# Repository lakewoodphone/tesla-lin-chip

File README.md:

# tesla-lin-chip

Tesla LIN reverse-engineering and anti-nag chip project. Covers passive LIN capture, active frame injection, Model 3/Y/X steering wheel volume control, and the custom dual-LIN ESP32-S3 Rev A PCB (JLCPCB order).

**Local path:** `C:\Users\ezabz\Code\tesla-lin-chip`
**GitHub:** `https://github.com/lakewoodphone/tesla-lin-chip`

Start with `START_HERE.md` when resuming. It now points to the current Rev A ESP32-S3 dual-LIN Model 3 active anti-nag path. Older XIAO/APG discovery notes are preserved under `docs/archive/legacy-xiao-2026-06-17/` and should be treated as historical evidence, not the active operating surface.

Current first-read docs:

```text
START_HERE.md
NEXT_STEPS.md
TOOLS.md
docs/README.md
docs/active/rev-a-model3-active-anti-nag.md
docs/active/model3-capture-data-index.md
```

Current Rev A helper:

```powershell
powershell -NoProfile -ExecutionPolicy Bypass -File tools\rev-a-active-model3.ps1 -Action Preflight
```

For the implementation plan that makes the bench, passive car testing, and final active-capable chip more robust, read `IMPLEMENTATION_ROADMAP.md`.

## Current Status

- Passive LIN receive is bench-verified at 19200 baud.
- Full no-car evidence passed on 2026-05-26 and again after APG reseat on 2026-05-27: 80/80 exact APG -> XIAO matches across raw IDs `0x00` through `0x3F`, with 0 APG failures.
- Active Model X bench TX is verified on the isolated bench. `model:x` + `antinag:start` produced more than 100 self-received `0x0C` frames with enhanced checksum and parity OK.
- Active improvements applied: bus-idle collision guard (2 ms silence before TX), realistic scroll payloads (non-zero B2/B3), and mirror/alive frame injection (`0x0D` at 500 ms via `mirror:on`).
- Active safety now reports reset reason, fault count, last fault, and lockout state. RX-integrity spikes or a dominant-line timeout while armed force active output off and block re-arm until `safe:off` is run after inspection.
- Repository default now builds `field_passive`; active TX is explicit via `bench_active_ble` or `chip_lab_active`.
- BLE service "TeslaAntiNag" in active builds exposes model (x/3/y/auto), mode (duty/always), period (5-120s), enable (on/off), status, and capabilities characteristics. Enable requires `safe:arm` first.
- BLE advertising was revalidated on 2026-05-27 after fixing invalid NimBLE advertising intervals; active lab builds report `advertising=yes` over serial.
- Car-day tooling enforces passive preflight and verifies `field_passive` firmware by default.
- APG known-ID raw fallback captures XIAO-generated active Model X frames after APG reseat: `active-apg-raw-proof.ps1` passed with 11 raw `ID=0x0C PID=0x4C` rows at `logs\lin-capture-20260527_212130.csv`.
- Model 3/Y steering LIN was captured on 2026-05-28. The confirmed left wheel control ID is `0x2A` (7 bytes) and right wheel control ID is `0x2B` (6 bytes). Left wheel byte[0] is `0x0D` volume up, `0x0B` volume down, `0x2C` click, `0x0C` idle. See `docs/model3y-steering-lin-2026-05-28.md`.
- `car_passthrough` is a new dual-transceiver firmware profile for the actual cut-wire bridge design. See `docs/model3y-passthrough-volume.md`.
- Final active-use hardware requires a custom dual-LIN passthrough PCB, not a one-LIN board. Current Rev A order core is `ESP32-S3-WROOM-1U-N8R8` plus 2x `TJA1021T/20`. See `docs/final-board-ordering-decision-2026-05-29.md`.

## Hard Stops

- Do not transmit on a vehicle LIN bus.
- Do not run `validate-xiao-bench.ps1`, `bench-evidence-suite.ps1`, `send-netanalyser-headless.ps1`, `antinag-replay.ps1`, or active firmware commands on a vehicle.
- Vehicle work starts passive only: APG passive monitor plus XIAO passive receive.
- Do not assume Model 3/Y IDs match Model X. Capture first, then label.
- Do not use the old `0x1A` Model 3/Y candidate for current Model 3 volume work; the confirmed left scroll wheel ID is `0x2A`.
- Do not use the old `C:\Users\ezabz\Code\Schematics\firmware\anti-nag-v1` path as active firmware.

## Hardware

| Component | Part | Notes |
|---|---|---|
| MCU | Seeed XIAO ESP32-C3 | USB CDC, normally COM4 |
| LIN analyzer | Microchip APGDT001 | VID `04D8`, PID `0A04`; PICkitS DLL is x86 |
| LIN transceiver | GODIYMODULES TJA1021 breakout | Logic header: `GND TX SLP RX`; bus header: `GND LIN INH VIN` |
| Level shifter | DIYables 4-channel bidirectional | HV=5V, LV=3.3V |
| PSU | Bench supply | 12V bus/module power |

## Wiring

Power and bus:

```text
PSU 12V -> APG VBAT / bus power
PSU 12V -> module VIN
PSU GND -> APG GND -> module GND -> level shifter GND -> XIAO GND
APG LINBUS pin 1 -> module LIN
XIAO 5V/VUSB -> module SLP and level shifter HV
XIAO 3V3 -> level shifter LV
```

Passive receive path:

```text
module RX -> level shifter HV1/A1 -> level shifter LV1/B1 -> XIAO D3/GPIO5
```

Active bench TX path:

```text
XIAO D2/GPIO4 -> level shifter LV2/B2 -> level shifter HV2/A2 -> module TX
```

Known wiring lesson from 2026-05-27: if `txd:low` makes XIAO D2 near 0V but LV2 stays near 3.3V, the D2 -> LV2 jumper is disconnected or on the wrong channel.

## Firmware

Main file: `src/main.cpp`

Core passive features:

- UART1 at 19200 baud on RX GPIO5/D3 and TX GPIO4/D2.
- Boundary-based parser: break/idle -> sync `0x55` -> PID -> data/checksum.
- Actual payload length is observed from frame boundary; `pred=<n>` is only the ID-class length hint.
- Protected-ID parity validation.
- Enhanced/classic checksum detection.
- Ring buffer of recent frames via `ring`.
- Runtime serial commands: `vehicle:`, `baud:`, `raw:`, `ring`, `stats`.
- USB serial fallback when WiFi is unavailable.

Active mode (`bench_active_ble` / `chip_lab_active`, bench only):

- Active TX requires serial `safe:arm` before any frame, BLE enable, TXD diagnostic, or custom `tx:` command can transmit. Use `safe:off` to stop and disarm.
- Two modes: `mode:duty` (burst UP -> DOWN every `period:N` ms, default 20s) or `mode:always` (constant alternation every 300ms).
- Double-click scroll wheel button: two fast presses toggles chip output on/off.
- Model profiles: `model:x` (`0x0C` confirmed), `model:3` (`0x2A` confirmed left scroll wheel), `model:y` (`0x2A` likely; verify passively), `model:auto`.
- Active commands: `safe:arm`, `safe:off`, `factory:reset`, `config`, `model`, `model:x`, `model:3`, `model:y`, `antinag:start`, `antinag:stop`, `antinag:single`, `vol:up`, `vol:down`, `vol:click`, `vol:idle`, `mode:duty`, `mode:always`, `period:20000`, `mirror:on`, `mirror:off`, `tx:`.
- Active event log: `events` prints recent RAM events and persisted NVS slots for boot, arm, config, start/stop, inhibits, and faults.
- Diagnostics: `txd:low`, `txd:high`, `txd:uart`.
- BLE: NimBLE config service with model/mode/period/enable plus status/capabilities. Advertises as "TeslaAntiNag". Double-click wheel button still toggles on/off only after arming.
- Active lab builds define `NO_WIFI`; BLE and USB serial are the active-lab control/evidence paths so missing shop WiFi cannot interfere with BLE advertising.
- NVS persisted config stores model/mode/period with version+CRC; active output always boots off/disarmed.

## Build And Flash

Build current repo default passive field firmware:

```powershell
cd C:\Users\ezabz\Code\xiao-lin-bench
python -m platformio run
```

Build every supported firmware target:

```powershell
powershell -NoProfile -ExecutionPolicy Bypass -File tools\build-all-envs.ps1
```

Build active bench firmware explicitly:

```powershell
python -m platformio run -e bench_active_ble
```

Build the dual-transceiver passthrough prototype:

```powershell
python -m platformio run -e car_passthrough
```

Upload to the XIAO on COM4:

```powershell
python -m platformio run -t upload --upload-port COM4
```

Monitor XIAO USB serial:

```powershell
python -m platformio device monitor --port COM4 --baud 115200 --dtr 1 --rts 0
```

If normal PlatformIO upload fails, use the documented `esptool --no-stub` fallback from `START_HERE.md`.

## Validation

Passive quick bench validation:

```powershell
powershell -NoProfile -ExecutionPolicy Bypass -File tools\validate-xiao-bench.ps1 -ComPort COM4 -Baud 19200 -BootWaitSeconds 4 -PerFrameTimeoutMs 2500
```

Full no-car evidence suite:

```powershell
.\tools\bench-evidence-suite.ps1 -VehicleId tesla-bench-full -ComPort COM4 -Baud 19200
```

Active Model X bench validation flow:

```powershell
# After flashing bench_active_ble firmware:
powershell -NoProfile -ExecutionPolicy Bypass -File tools\active-bench-proof.ps1 -ComPort COM4 -Model x -ConfirmBenchIsolation
```

Expected active proof: `ring` shows `ID=0x0C PID=0x4C [8B]` frames with `enhanced parity=OK` and `badChk=0 badPid=0` in `stats`.

Independent APG known-ID raw observer proof, bench only:

```powershell
powershell -NoProfile -ExecutionPolicy Bypass -File tools\active-apg-raw-proof.ps1 -Model x -DurationSeconds 6 -MinFrames 8 -ConfirmBenchIsolation
```

Expected APG raw proof: `PASS` with raw CSV rows for the selected model ID, `source=raw`. The script supports `-Model x|3|y|auto`, preflights APG initialization before active TX, forces continuous active mode during capture, restores duty mode afterward, and exits before transmit if APG is unavailable.

## Tooling

| Tool | Purpose | Vehicle-safe? |
|---|---|---|
| `tools/monitor-apg-lin-bus.ps1` | APG passive capture | Yes, receive-only |
| `tools/car-day-launcher.ps1` | Passive car-day APG/XIAO launcher | Yes, if used passive-only |
| `tools/build-all-envs.ps1` | Compile all firmware environments | Yes |
| `tools/new-capture-session.ps1` | Create manifest-backed capture folder | Yes |
| `tools/preflight-hardware-check.ps1` | Record physical preflight checks | Yes |
| `tools/full-bench-proof.ps1` | Build + passive proof; add `-RunActive -ConfirmBenchIsolation` for active/APG raw bench proof | No, bench only |
| `tools/validate-xiao-bench.ps1` | APG transmit -> XIAO receive validation | No, bench only |
| `tools/bench-evidence-suite.ps1` | Full APG/XIAO no-car evidence matrix | No, bench only |
| `tools/active-bench-proof.ps1` | XIAO active TX self-receive proof | No, bench only |
| `tools/active-apg-raw-proof.ps1` | XIAO active TX plus APG known-ID raw observer proof | No, bench only |
| `tools/prepare-model3y-car-day.ps1` | Pre-arrival APG/XIAO health check and `field_passive` flash | Yes |
| `tools/start-model3y-passive-capture.ps1` | Passive Model 3/Y capture wrapper with action windows | Yes, passive only |
| `tools/process-model3y-capture.ps1` | Analyze a capture session and emit candidate JSON | Yes, post-capture |
| `tools/stage-model3y-active-bench.ps1` | Apply reviewed 3/Y candidate and run bench-only active proofs | No, bench only |
| `tools/inject-vol-scroll.py` | Confirmed 0x2A left-volume active proof with JSON run logs | No, bench only |
| `tools/send-netanalyser-headless.ps1` | APG headless LIN transmit | No, bench only |
| `tools/antinag-replay.ps1` | APG anti-nag replay sequence | No, bench only |
| `tools/serial-to-lin-events.ps1` | XIAO USB serial -> secretary API | Passive if source is passive |
| `tools/analyze-lin-capture.py` | Post-capture analysis, Tesla ID reference, action-window ranking | Yes, post-capture |
| `tools/summarize-lin-capture.ps1` | Quick APG CSV summary | Yes, post-capture |
| `tools/lin-payload-calc.py` | Payload/checksum calculator | Reference only |

APG tools must run through 32-bit PowerShell when they load `PICkitS.dll`:

```powershell
cmd /c %WINDIR%\SysWOW64\WindowsPowerShell\v1.0\powershell.exe -STA -NoProfile -ExecutionPolicy Bypass -File tools\monitor-apg-lin-bus.ps1 -Baud 19200
```

## Evidence And Docs

- `START_HERE.md` - canonical current handoff.
- `BENCH_EVIDENCE.md` - passive and active bench evidence.
- `ACTIVE_INJECTOR.md` - active bench wiring, operation, and diagnostics.
- `IMPLEMENTATION_ROADMAP.md` - full roadmap for bench robustness, passive car testing, and final active-capable chip development.
- `NEXT_STEPS.md` - current work plan.
- `TOOLS.md` - tool reference.
- `docs/archive/` - old passive-only and capture-history notes.
- `docs/final-board-ordering-decision-2026-05-29.md` - current direct Rev A order decision.
- `docs/final-chip-architecture.md` - current dual-LIN active passthrough board architecture.

## Known Issues

| Issue | Current understanding |
|---|---|
| APG NetworkAnalyser event/display modes log zero rows for XIAO-generated active frames | Settled: use `monitor-apg-lin-bus.ps1 -RawFallback -RawFallbackId 0x0C` or `active-apg-raw-proof.ps1` for known-ID bench observation. Generic vehicle discovery still uses normal passive event capture first. |
| APGDT001 reports `CM_PROB_FAILED_START` / `Error sending script` | Reseat/replug or use elevated PnP restart before APG-dependent tests. The May 27 physical reseat recovered APG to `CM_PROB_NONE`, and passive plus APG raw proofs passed afterward. |
| XIAO WiFi reports `NO_AP_FOUND` | Use USB serial and `serial-to-lin-events.ps1` unless WiFi credentials are repaired |
| `PermissionError` on COM4 | A serial monitor is holding the port; stop PlatformIO/terminal process |
| Direct `send-apg-lin-frame.ps1` baud looks wrong | Use NetworkAnalyser-based tools for real validation |
| Holding TXD low does not always pull LIN low forever | LIN dominant-timeout can release the bus; validate with real frames and ring buffer |

## Repository Structure

```
tesla-lin-chip/
├── README.md                     This file — project overview and wiring reference
├── START_HERE.md                 Canonical current handoff — start here every session
├── BENCH_EVIDENCE.md             Passive and active bench evidence summary
├── ACTIVE_INJECTOR.md            Active TX bench wiring, operation, and diagnostics
├── IMPLEMENTATION_ROADMAP.md     Full roadmap: bench → passive car → final chip
├── NEXT_STEPS.md                 Current work plan
├── TOOLS.md                      Tool reference
├── platformio.ini                PlatformIO build config (passive default + active envs)
│
├── src/                          XIAO ESP32-C3 firmware
│   ├── main.cpp                  v5.1 — build profiles, safe arm gate, BLE, ring buffer
│   ├── car_passthrough.cpp       Dual-transceiver passthrough firmware prototype
│   └── secrets.h.example         WiFi/API settings template
│
├── hardware/
│   └── tesla-dual-lin-rev-a/     Rev A PCB — ESP32-S3-WROOM-1U-N8R8 + 2x TJA1021T/20
│       ├── kicad/                KiCad schematic + PCB (tesla-dual-lin-rev-a.kicad_sch/pcb)
│       ├── bom/                  BOM strategy, cost model, supplier shortlist
│       ├── build/                Generated Gerbers, drill files
│       ├── manufacturing/        JLCPCB order files
│       ├── electrical/           Constraint files
│       └── tests/                DRC/ERC reports
│
├── docs/
│   ├── final-board-ordering-decision-2026-05-29.md  Rev A order decision
│   ├── final-chip-architecture.md                   Dual-LIN active board architecture
│   ├── model3y-steering-lin-2026-05-28.md           Model 3/Y confirmed ID map (0x2A left, 0x2B right)
│   ├── model3y-passthrough-volume.md                Cut-wire passthrough architecture
│   ├── bench-revalidation-2026-05-27.md             BLE fix + APG reseat proof
│   ├── chip-sourcing-shortlist-2026-05-29.md        ESP32-S3 + TJA1021 supplier shortlist
│   ├── secure-provisioning-anti-cloning-2026-05-29.md  nRF5340 anti-cloning design notes
│   ├── single-board-rev-a-product-spec-2026-05-29.md   Rev A product spec
│   ├── reports/                  Field analysis reports from vehicle visits
│   └── archive/                  Historical passive/capture notes
│
├── research/
│   ├── directives/               Research directives (ESP32, LIN, PCB, Tesla purchase)
│   └── responses/                Research responses and synthesis documents
│
├── knowledge/
│   └── hardware/                 Hardware knowledge base (TSL family, anti-nag landscape, BOM strategy)
│
├── tools/                        PowerShell + Python operational scripts
│   ├── tesla-tsl5-lin-capture.ps1     LIN capture via FX2/Sigrok for TSL5 bench
│   ├── tesla-tsl5-bench-readiness.ps1 TSL5 bench readiness check
│   └── ... (see TOOLS.md for full list)
│
├── captures/
│   ├── sigrok/                   Raw .sr Sigrok captures (FX2 device, Model X field sessions)
│   └── lin-csv/                  (use logs/ for CSV captures from the bench)
│
├── logs/                         Bench CSV captures, active proof logs, bench evidence archives
├── photos/                       Vehicle visit photos (Model X SCCM, steering wheel access points)
├── audit-logs/                   Session audit logs (Tesla deal, bench setup sessions)
└── boards/                       Board JSON definitions (ESP32-S3 N8R8)
```

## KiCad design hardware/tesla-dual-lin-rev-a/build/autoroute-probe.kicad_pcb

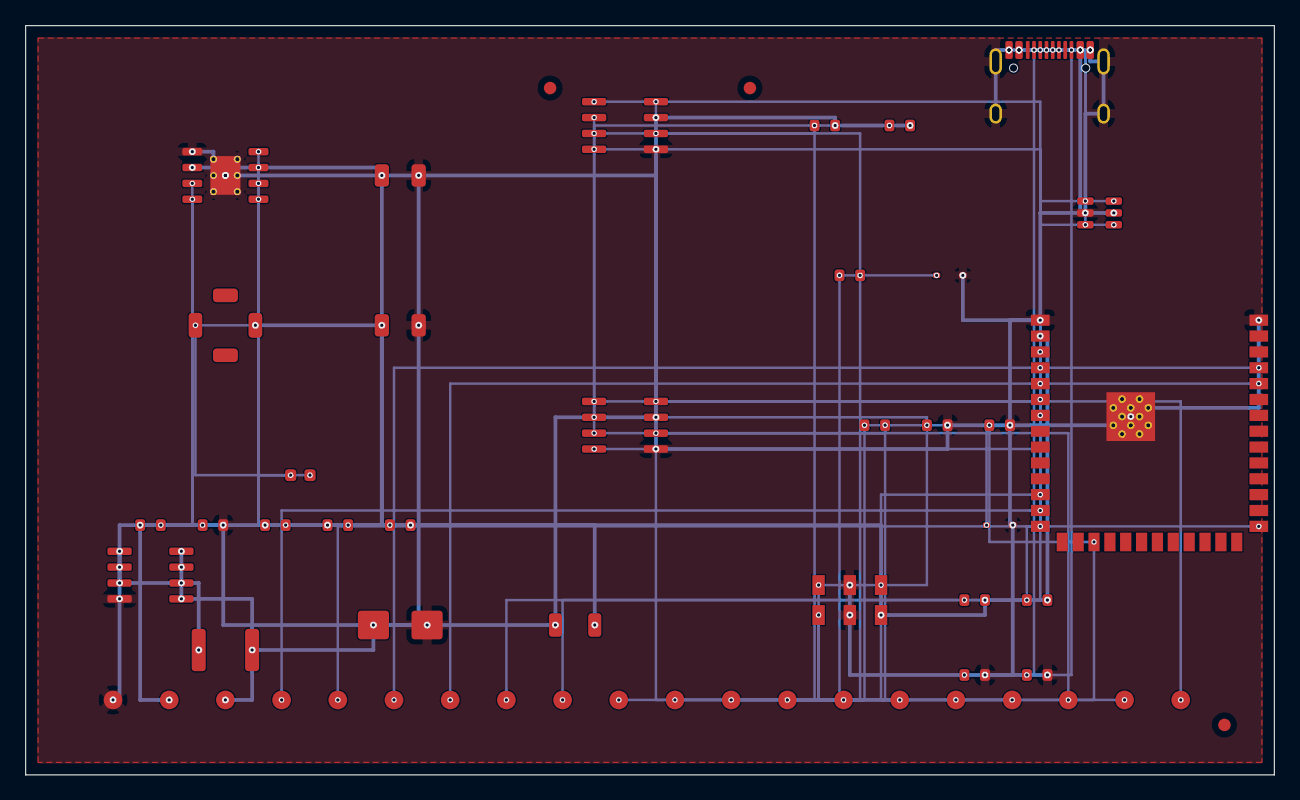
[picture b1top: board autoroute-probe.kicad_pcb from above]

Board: 4 copper layers, 100.0 x 60.0 mm, 55 parts (0 on the bottom side), 35 nets.

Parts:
C_3V3: 22uF 10V; C_1206_3216Metric
C_BST: 100nF; C_0603_1608Metric
C_IN: 10uF 50V; C_1206_3216Metric
D1: SMBJ24A; D_SMB
D2: LIN_A ESD; D_SOD-323
D3: LIN_B ESD; D_SOD-323
D4: USB ESD; SOT-23-6
F1: 1812 PPTC; Fuse_1812_4532Metric
FB1: 1206 ferrite; L_1206_3216Metric
FID1, FID2, FID3: FID; Fiducial_1mm_Mask2mm
J1: USB-C; USB_C_Receptacle_HRO_TYPE-C-31-M-12
L1: 10uH; L_Bourns_SRU5016_5.2x5.2mm
Q1: AO4407A PFET; SOIC-8_3.9x4.9mm_P1.27mm
R_ARMSENSE_PD: 0603; R_0603_1608Metric
R_BOOT: 0603; R_0603_1608Metric
R_BUCK_EN: 0603; R_0603_1608Metric
R_BUCK_RON: 0603; R_0603_1608Metric
R_CC1, R_CC2: 0603; R_0603_1608Metric
R_EN: 0603; R_0603_1608Metric
R_FB_BOT: 0603; R_0603_1608Metric
R_FB_TOP: 0603; R_0603_1608Metric
R_LINA_SER: 0603; R_0603_1608Metric
R_LINB_SER: 0603; R_0603_1608Metric
R_LINEN_PD: 0603; R_0603_1608Metric
R_PGOOD_PU: 0603; R_0603_1608Metric
R_WAKE_A: 0603; R_0603_1608Metric
R_WAKE_B: 0603; R_0603_1608Metric
SW1: DPDT ARM; SW_DPDT_CK_JS202011JCQN
TP1: GND; TestPoint_Pad_D1.5mm
TP2: 3V3; TestPoint_Pad_D1.5mm
TP3: VBAT; TestPoint_Pad_D1.5mm
TP4: USB-; TestPoint_Pad_D1.5mm
TP5: USB+; TestPoint_Pad_D1.5mm
TP6: UART_TX; TestPoint_Pad_D1.5mm
TP7: UART_RX; TestPoint_Pad_D1.5mm
TP8: EN; TestPoint_Pad_D1.5mm
TP9: BOOT; TestPoint_Pad_D1.5mm
TP10: LIN_A; TestPoint_Pad_D1.5mm
TP11: LIN_B; TestPoint_Pad_D1.5mm
TP12: LIN_A_TJA; TestPoint_Pad_D1.5mm
TP13: LIN_B_TJA; TestPoint_Pad_D1.5mm
TP14: LIN_EN; TestPoint_Pad_D1.5mm
TP15: LIN_EN_DRV; TestPoint_Pad_D1.5mm
TP16: ARM; TestPoint_Pad_D1.5mm
TP17: WAKE_A; TestPoint_Pad_D1.5mm
TP18: WAKE_B; TestPoint_Pad_D1.5mm
TP19: INH_A; TestPoint_Pad_D1.5mm
TP20: INH_B; TestPoint_Pad_D1.5mm
U1: ESP32-S3-WROOM-1U
U2: TJA1021T car; SOIC-8_3.9x4.9mm_P1.27mm
U3: TJA1021T wheel; SOIC-8_3.9x4.9mm_P1.27mm
U4: LM5164DDA; HSOP-8-1EP_3.9x4.9mm_P1.27mm_EP2.41x3.1mm_ThermalVias

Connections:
3V3: C_3V3.1, L1.2, R_BOOT.2, R_EN.2, R_FB_TOP.1, R_PGOOD_PU.2, SW1.6, TP2.1, U1.2
ARM_SENSE: R_ARMSENSE_PD.1, SW1.4, TP16.1, U1.17
BOOT_GPIO0: R_BOOT.1, TP9.1, U1.27
BUCK_BST: C_BST.1, U4.7
BUCK_EN: R_BUCK_EN.2, U4.3
BUCK_FB: R_FB_BOT.1, R_FB_TOP.2, U4.5
BUCK_PGOOD: R_PGOOD_PU.1, U4.6
BUCK_RON: R_BUCK_RON.2, U4.4
BUCK_SW: C_BST.2, L1.1, U4.8
CC1: J1.A5, R_CC1.1
CC2: J1.B5, R_CC2.1
EN: R_EN.1, TP8.1, U1.3
GND: C_3V3.2, C_IN.2, D1.2, D2.2, D3.2, D4.2, J1.A1, J1.A12, J1.B1, J1.B12, J1.SH, Q1.4, R_ARMSENSE_PD.2, R_CC1.2, R_CC2.2, R_FB_BOT.2, R_LINEN_PD.2, SW1.2, SW1.5, TP1.1, U1.1, U1.40, U1.41, U2.5, U3.5, U4.1, U4.9
INH_A_TP: TP19.1, U2.8
INH_B_TP: TP20.1, U3.8
LIN_A: D2.1, R_LINA_SER.1, TP10.1
LIN_A_RXD: U1.4, U2.1
LIN_A_TJA: R_LINA_SER.2, TP12.1, U2.6
LIN_A_TXD: U1.5, U2.4
LIN_B: D3.1, R_LINB_SER.1, TP11.1
LIN_B_RXD: U1.6, U3.1
LIN_B_TJA: R_LINB_SER.2, TP13.1, U3.6
LIN_B_TXD: U1.7, U3.4
LIN_EN: R_LINEN_PD.1, SW1.1, TP14.1, U2.2, U3.2
LIN_EN_DRIVE: SW1.3, TP15.1, U1.12
UART0_RX: TP7.1, U1.36
UART0_TX: TP6.1, U1.37
USB_D_MINUS: D4.1, D4.6, J1.A7, J1.B7, TP4.1, U1.13
USB_D_PLUS: D4.3, D4.4, J1.A6, J1.B6, TP5.1, U1.14
USB_VBUS: D4.5, J1.A4, J1.A9, J1.B4, J1.B9
VBAT_FILTERED: C_IN.1, FB1.2, R_BUCK_EN.1, R_BUCK_RON.1, U4.2
VBAT_IN: F1.1, Q1.1, Q1.2, Q1.3
VBAT_PROTECTED: D1.1, F1.2, FB1.1, Q1.5, Q1.6, Q1.7, Q1.8, R_WAKE_A.2, R_WAKE_B.2, TP3.1, U2.7, U3.7
WAKE_A_N: R_WAKE_A.1, TP17.1, U2.3
WAKE_B_N: R_WAKE_B.1, TP18.1, U3.3

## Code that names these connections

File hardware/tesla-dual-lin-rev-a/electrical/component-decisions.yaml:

project: tesla-dual-lin-rev-a
revision: A
decision_date: 2026-05-29
goal: affordable robust 100-unit-ready dual-LIN ESP32-S3 PCBA

source_backing:
  completed_research_artifacts:
    - personal-secretary-mvp/docs/research/responses/2026-05-29-100-unit-dual-lin-ble-passthrough-board-manufacturing-plan-ad722f1f.md
    - personal-secretary-mvp/docs/research/responses/2026-05-29-dual-lin-esp32-s3-rev-a-schematic-and-pcba-design-rules-68f254d3.md
    - personal-secretary-mvp/docs/research/responses/2026-05-29-cost-optimized-rev-a-dual-lin-esp32-s3-pcba-bom-research-8380af65.md
  live_closure_job:
    job_id: f19c0816-ef6a-44c3-bc8c-167cc22b492e
    status_at_decision_time: running
    note: targeted closure job is durable tracking; Rev A decisions below use completed research plus local KiCad/NXP symbol verification.
  local_source_checks:
    - source: KiCad 10 Interface_CAN_LIN.kicad_sym symbol TJA1021xT
      path: C:/Users/ezabz/AppData/Local/Programs/KiCad/10.0/share/kicad/symbols/Interface_CAN_LIN.kicad_sym
      finding: SOIC-8 symbol maps RXD=1, SLP_N=2, WAKE_N=3, TXD=4, GND=5, LIN=6, VBAT=7, INH=8.
    - source: NXP TJA1021 datasheet URL referenced by KiCad symbol and research artifact
      url: https://www.nxp.com/docs/en/data-sheet/TJA1021.pdf
      note: direct NXP download was blocked locally; LCSC/Farnell mirrors were downloaded for later manual review.
    - source: Espressif ESP32-S3-WROOM-1/1U datasheet
      url: https://documentation.espressif.com/esp32-s3-wroom-1_wroom-1u_datasheet_en.pdf
      finding: native USB uses GPIO19 D- and GPIO20 D+; module requires 3.3V rail sized for radio peaks.
    - source: TI LM5164 datasheet and KiCad 10 Regulator_Switching symbol LM5164DDA
      url: https://www.ti.com/product/LM5164
      finding: LM5164DDA is an active 6V-100V 1A synchronous buck in 8-pin SOIC PowerPAD; symbol maps GND=1, VIN=2, EN/UVLO=3, RON=4, FB=5, PGOOD=6, BST=7, SW=8, EP=9.
    - source: Tesla steering-wheel LIN connector research artifact
      path: personal-secretary-mvp/docs/research/responses/2026-05-31-research-directive-tesla-steering-wheel-lin-harness-connector-identification-5cdd8b12.md
      finding: Public Tesla Model Y SOP6 steering-wheel switch inline data identifies a 4-cavity VBAT/GND/unused/LIN interface, but does not prove the OEM physical connector family; Rev A uses Molex Micro-Fit 3.0 43650-0415 board-side service connectors plus adapter pigtails.

tja1021_soic8:
  selected_mpn: TJA1021T/20/C,118
  package: SOIC-8
  kicad_symbol: Interface_CAN_LIN:TJA1021xT
  kicad_footprint: Package_SO:SOIC-8_3.9x4.9mm_P1.27mm
  pinout:
    "1": RXD
    "2": SLP_N
    "3": WAKE_N
    "4": TXD
    "5": GND
    "6": LIN
    "7": VBAT
    "8": INH
  rev_a_mode_decisions:
    bus_role: responder_or_bridge_node_only
    default_no_master_pullup_populated: true
    optional_dnp_master_pullup_footprints: true
    reason: Tesla vehicle side is assumed to provide the LIN commander/master bias; Rev A leaves strong 1k plus diode LIN master pullups DNP by default, with footprints available only if bench evidence proves an isolated commanded segment requires one.
    vbat: VBAT_PROTECTED with 100nF plus 1uF local decoupling per transceiver
    lin: 10R series resistor plus PESD1LIN-class ESD at each harness entry
    slp_n: common post-switch LIN_EN net, external 100k pulldown, safe switch throw hard-ties LIN_EN to GND
    wake_n: pulled high to VBAT_PROTECTED through 100k and exposed only as optional test net; no MCU GPIO for Rev A
    inh: not used to enable the buck regulator; exposed only as optional no-load test net
    txd: firmware must set TXD pins to recessive/idle before asserting LIN_EN_DRIVE; SLP_N gate is the hardware safety layer
    rxd: direct 3.3V-compatible MCU input, no level shifter
  default_off_chain:
    - MCU reset/blank/bootloader leaves LIN_EN_DRIVE low or high-Z.
    - R_LINEN_PD holds LIN_EN low.
    - SW1 safe position shorts LIN_EN to GND regardless of firmware.
    - SW1 second pole shorts ARM_SENSE to GND in safe/off and to 3V3 in armed position.
    - Both TJA1021 SLP_N pins stay low, keeping transceivers asleep.
    - Firmware can enter normal LIN only after physical arm is on and safe:arm asserts LIN_EN_DRIVE.
  physical_arm_switch:
    type: DPDT slide switch
    pole_a_common: LIN_EN
    pole_a_safe_throw: GND
    pole_a_arm_throw: LIN_EN_DRIVE
    pole_b_common: ARM_SENSE
    pole_b_safe_throw: GND
    pole_b_arm_throw: 3V3
    arm_sense_default: 100k pulldown to GND
    reason: firmware must be able to read the physical arm position before it asserts LIN_EN_DRIVE.

esp32_s3_wroom_1u:
  selected_mpn: ESP32-S3-WROOM-1U-N8R8
  lcsc: C2980300
  footprint: RF_Module:ESP32-S3-WROOM-1U
  footprint_status: verify_against_espressif_land_pattern_before_fab
  pin_policy:
    usb_d_minus: GPIO19
    usb_d_plus: GPIO20
    uart0_tx_recovery_pad: GPIO43
    uart0_rx_recovery_pad: GPIO44
    boot: GPIO0 with 10k pullup to 3V3 and pogo/button pull-to-GND
    reset: EN with 10k pullup to 3V3, 1uF to GND, pogo/button pull-to-GND
    gpio46: do not drive high during boot; leave unused or pad-only if exposed later
    lin_a_rxd: GPIO4
    lin_a_txd: GPIO5
    lin_b_rxd: GPIO6
    lin_b_txd: GPIO7
    lin_en_drive: GPIO8
    arm_sense: GPIO9
  notes:
    - GPIO4-GPIO9 are intentionally kept away from native USB and UART recovery pins.
    - Final schematic review must confirm module pins are not reserved by flash/PSRAM internals on the N8R8 module.

power_front_end:
  default_path: VBAT_IN -> Q1 reverse polarity PFET -> F1 PPTC -> D1 TVS -> FB1 ferrite/filter -> U4 buck -> 3V3
  rev_a_default_buck:
    class: LM5164DDA 100V 1A synchronous buck
    footprint_target: Package_SO:HSOP-8-1EP_3.9x4.9mm_P1.27mm_EP2.41x3.1mm_ThermalVias
    reason: accessible TI datasheet and KiCad symbol, much stronger automotive transient margin for first articles, integrated synchronous rectifier, low quiescent current, and no loop compensation components
    feedback_assumption: 1.2V reference from TI datasheet
    feedback_values:
      top: 174k 1% 0603
      bottom: 100k 1% 0603
      expected_vout: 3.29V
    ron_resistor: 200k 1% preliminary; finalize with TI WEBENCH or LM5164 switching-frequency equation before production release
    inductor: 10uH shielded, Isat >= 1.5A, DCR low enough for 500mA continuous
    input_caps: 10uF 50V X7R plus 100nF 50V at VIN/GND
    output_caps: 22uF 10V X7R plus 100nF at VOUT/GND
    bootstrap_cap: 100nF from BST to SW
    enable_policy: always-on from protected input for Rev A; do not use TJA1021 INH to gate buck
  later_cost_down_buck:
    class: MP2459DT-LF-Z/MP1584 36V-class buck
    trigger: only after exact datasheet, pinout, feedback reference, and bench transient margins are verified
  input_protection:
    reverse_polarity: AO4407A-class P-channel MOSFET, SO-8, Vds margin >= 30V, current margin >= 2A
    overcurrent: 1812 PPTC, 0.5A to 0.75A hold, voltage rating suitable for vehicle rail
    low_cost_tvs: SMBJ24A or SMBJ26A, SMB package
    robust_tvs: SM8S33A or SM8S36A, larger high-surge automotive TVS
    filter: 1206 ferrite 600R@100MHz, 2A class plus 47uF 35V-50V bulk near buck zone

usb_service:
  connector: TYPE-C-31-M-12-class USB2 receptacle
  cc: two 5.1k 1% 0603 Rd resistors to GND
  data: GPIO19/GPIO20 routed as D-/D+ pair through low-cap USB ESD near connector
  vbus_policy: service/detect only in Rev A; no USB-to-vehicle backfeed
  optional_usb_power: blocked until a defined ORing/power-mux circuit is added and tested

lin_protection:
  per_line:
    series_resistor: 10R 0603, placed near TJA1021 LIN pin or between ESD and transceiver per layout review
    esd: PESD1LIN/PESD1CAN-class single-line automotive ESD, SOD-323 or SOT-23
  forbidden_for_rev_a:
    - adding LIN master pullup/diode on either side without bench proof
    - tying car-side and wheel-side LIN together except through intentional test/bypass fixture

known_remaining_blockers:
  - Physical Tesla OEM harness connector family and pin geometry still require mechanical inspection for the adapter pigtail; board-side J2/J3 service connectors are now Molex Micro-Fit 3.0 43650-0415 4-circuit headers.
  - LM5164 RON/frequency, ripple network, inductor, and capacitor values must be checked with TI calculator/WEBENCH before production release.
  - ESP32-S3-WROOM-1U KiCad footprint must be compared against Espressif land pattern and paste recommendations.
  - First article must prove no LIN dominant pulse during reset, bootloader, safe/off, arming, firmware crash, and brownout.

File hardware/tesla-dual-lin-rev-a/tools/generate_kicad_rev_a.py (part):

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    "USB_VBUS",
    "CC1",
    "CC2",
    "BOOT_GPIO0",
    "EN",
    "UART0_TX",
    "UART0_RX",
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    u1_nets = {1: "GND", 2: "3V3", 3: "EN", 4: "LIN_A_RXD", 5: "LIN_A_TXD",
               6: "LIN_B_RXD", 7: "LIN_B_TXD", 12: "LIN_EN_DRIVE",
               13: "USB_D_MINUS", 14: "USB_D_PLUS", 17: "ARM_SENSE",
               27: "BOOT_GPIO0", 36: "UART0_RX", 37: "UART0_TX",
               40: "GND", 41: "GND"}
    components = [
        component("U1","ESP32-S3-WROOM-1U-N8R8","RF_Module:ESP32-S3-WROOM-1U", 41, u1_nets, 92, 112),
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        component("R_CC1","5.1k","Resistor_SMD:R_0603_1608Metric", 2, {1:"CC1",2:"GND"}, 198, 94),
        component("R_CC2","5.1k","Resistor_SMD:R_0603_1608Metric", 2, {1:"CC2",2:"GND"}, 198, 106),
        component("R_EN1","10k","Resistor_SMD:R_0603_1608Metric", 2, {1:"EN",2:"3V3"}, 198, 118),
        component("R_BOOT1","10k","Resistor_SMD:R_0603_1608Metric", 2, {1:"BOOT_GPIO0",2:"3V3"}, 198, 130),
        component("R_LINEN_PD1","100k","Resistor_SMD:R_0603_1608Metric", 2, {1:"LIN_EN",2:"GND"}, 198, 142),
        component("R_ARMSENSE_PD1","100k","Resistor_SMD:R_0603_1608Metric", 2, {1:"ARM_SENSE",2:"GND"}, 198, 154),
        component("R_WAKE_A1","100k","Resistor_SMD:R_0603_1608Metric", 2, {1:"WAKE_A_N",2:"VBAT_PROTECTED"}, 198, 166),
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        component("C_U3_DEC1","100nF 50V","Capacitor_SMD:C_0603_1608Metric", 2, {1:"VBAT_PROTECTED",2:"GND"}, 320, 78),
        component("C_U4_DEC1","100nF 50V","Capacitor_SMD:C_0603_1608Metric", 2, {1:"VBAT_FILTERED",2:"GND"}, 320, 90),
    ]
    tp_labels = "GND 3V3 VBAT USB- USB+ UART_TX UART_RX EN BOOT LIN_A LIN_B LIN_A_TJA LIN_B_TJA LIN_EN LIN_EN_DRV ARM WAKE_A WAKE_B INH_A INH_B".split()
    tp_nmap = {"GND":"GND","3V3":"3V3","VBAT":"VBAT_PROTECTED","USB-":"USB_D_MINUS","USB+":"USB_D_PLUS",
               "UART_TX":"UART0_TX","UART_RX":"UART0_RX","EN":"EN","BOOT":"BOOT_GPIO0",
               "LIN_A":"LIN_A","LIN_B":"LIN_B","LIN_A_TJA":"LIN_A_TJA","LIN_B_TJA":"LIN_B_TJA",
               "LIN_EN":"LIN_EN","LIN_EN_DRV":"LIN_EN_DRIVE","ARM":"ARM_SENSE",
               "WAKE_A":"WAKE_A_N","WAKE_B":"WAKE_B_N","INH_A":"INH_A_TP","INH_B":"INH_B_TP"}
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    inst.append(FootprintInstance("U1","ESP32-S3-WROOM-1U","RF_Module:ESP32-S3-WROOM-1U",(90,32),0,
        pad_nets={1:"GND",2:"3V3",3:"EN",4:"LIN_A_RXD",5:"LIN_A_TXD",6:"LIN_B_RXD",7:"LIN_B_TXD",
                  12:"LIN_EN_DRIVE",13:"USB_D_MINUS",14:"USB_D_PLUS",17:"ARM_SENSE",
                  27:"BOOT_GPIO0",36:"UART0_RX",37:"UART0_TX",40:"GND",41:"GND"}))
    inst.append(FootprintInstance("SW1","DPDT ARM","Button_Switch_SMD:SW_DPDT_CK_JS202011JCQN",
                                   (66,46),0,pad_nets={1:"LIN_EN",2:"GND",3:"LIN_EN_DRIVE",4:"ARM_SENSE",5:"GND",6:"3V3"}))
    inst.append(FootprintInstance("J1","USB-C","Connector_USB:USB_C_Receptacle_HRO_TYPE-C-31-M-12",
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    inst.append(FootprintInstance("D4","USB ESD","Package_TO_SOT_SMD:SOT-23-6",(86,15),0,
        pad_nets={1:"USB_D_MINUS",2:"GND",3:"USB_D_PLUS",4:"USB_D_PLUS",5:"USB_VBUS",6:"USB_D_MINUS"}))
    for idx, (ref, nets) in enumerate([
        ("R_EN1",{1:"EN",2:"3V3"}), ("R_BOOT1",{1:"BOOT_GPIO0",2:"3V3"}),
        ("R_CC1",{1:"CC1",2:"GND"}), ("R_CC2",{1:"CC2",2:"GND"}),
    ]):
        inst.append(FootprintInstance(ref,"0603",pas,(76+(idx%2)*5,44+(idx//2)*4),0,pad_nets=nets))
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    inst.append(FootprintInstance("C_EN1","1uF 10V",c0603,(86,46),0,pad_nets={1:"EN",2:"GND"}))

    # TP row (y=50, x=7..92)
    tp_labels = "GND 3V3 VBAT USB- USB+ UART_TX UART_RX EN BOOT LIN_A LIN_B LIN_A_TJA LIN_B_TJA LIN_EN LIN_EN_DRV ARM WAKE_A WAKE_B INH_A INH_B".split()
    tp_nmap = {"GND":"GND","3V3":"3V3","VBAT":"VBAT_PROTECTED","USB-":"USB_D_MINUS","USB+":"USB_D_PLUS",
               "UART_TX":"UART0_TX","UART_RX":"UART0_RX","EN":"EN","BOOT":"BOOT_GPIO0",
               "LIN_A":"LIN_A","LIN_B":"LIN_B","LIN_A_TJA":"LIN_A_TJA","LIN_B_TJA":"LIN_B_TJA",
               "LIN_EN":"LIN_EN","LIN_EN_DRV":"LIN_EN_DRIVE","ARM":"ARM_SENSE",
               "WAKE_A":"WAKE_A_N","WAKE_B":"WAKE_B_N","INH_A":"INH_A_TP","INH_B":"INH_B_TP"}
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
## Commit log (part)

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2026-05-27 feat: Tesla LIN bench v4 - full firmware, tooling, docs
    - Firmware v4: boundary-based LIN parser, ring buffer, runtime serial commands
    - APGDT001 + TJA1021 + level shifter + XIAO ESP32-C3 hardware validated
    - Bench validation PASS: ID=0x0C, 0x10, 0x22, 0x3C enhanced/classic
    - Anti-nag replay tool: alternating UP/DOWN scroll with correct checksums
    - Python capture analyzer with Tesla ID reference tables
    - Car-day launcher: unified entry point for Model 3/Y/X capture
2026-05-27 feat: add no-car LIN bench evidence pipeline
2026-05-27 feat: add multi-model active anti-nag injector and TX wiring docs
2026-05-27 chore: default ACTIVE_MODE off — uncomment locally for active builds
2026-05-27 fix: validate active LIN TX bench path
2026-05-27 docs: refresh active LIN bench handoff
2026-05-27 tools: add APG passive mode diagnostics
2026-05-27 tools: capture active LIN frames via APG raw fallback
2026-05-27 firmware: bus-idle collision guard, realistic payloads, mirror injection
2026-05-27 v5: Enable ACTIVE_MODE by default, add NimBLE BLE config service with model/mode/period/enable characteristics, deferred advertising retry, fix BLE API for NimBLE 2.5.0, update START_HERE.md
2026-05-27 docs: update all docs for v5 BLE defaults, fix stale ACTIVE_MODE/BLE references, add audit log
2026-05-28 chore: harden LIN bench roadmap and safety gates
2026-05-28 fix: harden active bench BLE proof
2026-05-28 fix: prove APG reseat bench recovery
2026-05-28 feat: script model 3y capture workflow
2026-05-29 Document dual LIN passthrough board decision
2026-06-01 Add Tesla Dual LIN Rev A hardware package
2026-06-04 Document JLC D4 L1 replacement supplement
2026-06-04 Mark D4 L1 issue as mass-order blocker
2026-06-17 Consolidate all Tesla LIN project assets into tesla-lin-chip
    - Rename repo from xiao-lin-bench to tesla-lin-chip
    - Add docs/reports/: 4 Tesla field analysis and bench handoff reports
    - Add research/directives/: 12 Tesla/LIN/ESP32 research directives (019,022,027,044-047,052-056)
    - Add research/responses/: 46+ Tesla/dual-LIN research responses and syntheses
    - Add knowledge/hardware/: 12 Tesla TSL hardware knowledge base files
    - Add captures/sigrok/: 4 raw Sigrok .sr captures from Model X field sessions and FX2 preflight
2026-06-17 Add all bench logs, Gerbers, fab files, and design artifacts — full repo preservation
    Previously gitignored:
    - logs/: 121 bench CSV captures, active proof logs, bench-evidence session archives
    - hardware/tesla-dual-lin-rev-a/build/fab/: all Gerbers, drill, BOM, CPL (JLCPCB manufacturing package)
    - hardware/tesla-dual-lin-rev-a/build/first-article-records/: Rev A order dry-run records
    - hardware/tesla-dual-lin-rev-a/build/: all DRC/ERC reports, routing intermediate files
    - hardware/tesla-dual-lin-rev-a/build/quote/jlcpcb-mini-order-2026-05-31/: first quote package
